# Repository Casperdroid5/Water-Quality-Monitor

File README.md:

# Water Quality Monitor

This document outlines my contribution to the Water Quality Monitor project during my internship at the Health Concept Lab.

## Overview

The Water Quality Monitor utilizes a Raspberry Pi running Raspbian as the main controller and computer, along with a custom-designed PCB for circuit layout. Hardware control, GUI, and data processing are implemented using Python.

## Design Process

The design process involved selecting suitable hardware components, designing the PCB layout, and programming the firmware in Python.

1. **Hardware Selection**: Chose appropriate sensors, actuators, and electronic components to suit the needs of the clients setup.
2. **PCB Design**: Created a custom PCB layout to ensure optimal circuit connections.
3. **Firmware Development**: Developed the firmware using Python to enable hardware communication.
## Testing

Comprehensive testing was conducted to ensure accuracy and reliability.

1. **Hardware Testing**: Verified proper functionality of each hardware component on the printed circuitboard.
2. **Software Testing**: Thoroughly tested firmware for peripherals.

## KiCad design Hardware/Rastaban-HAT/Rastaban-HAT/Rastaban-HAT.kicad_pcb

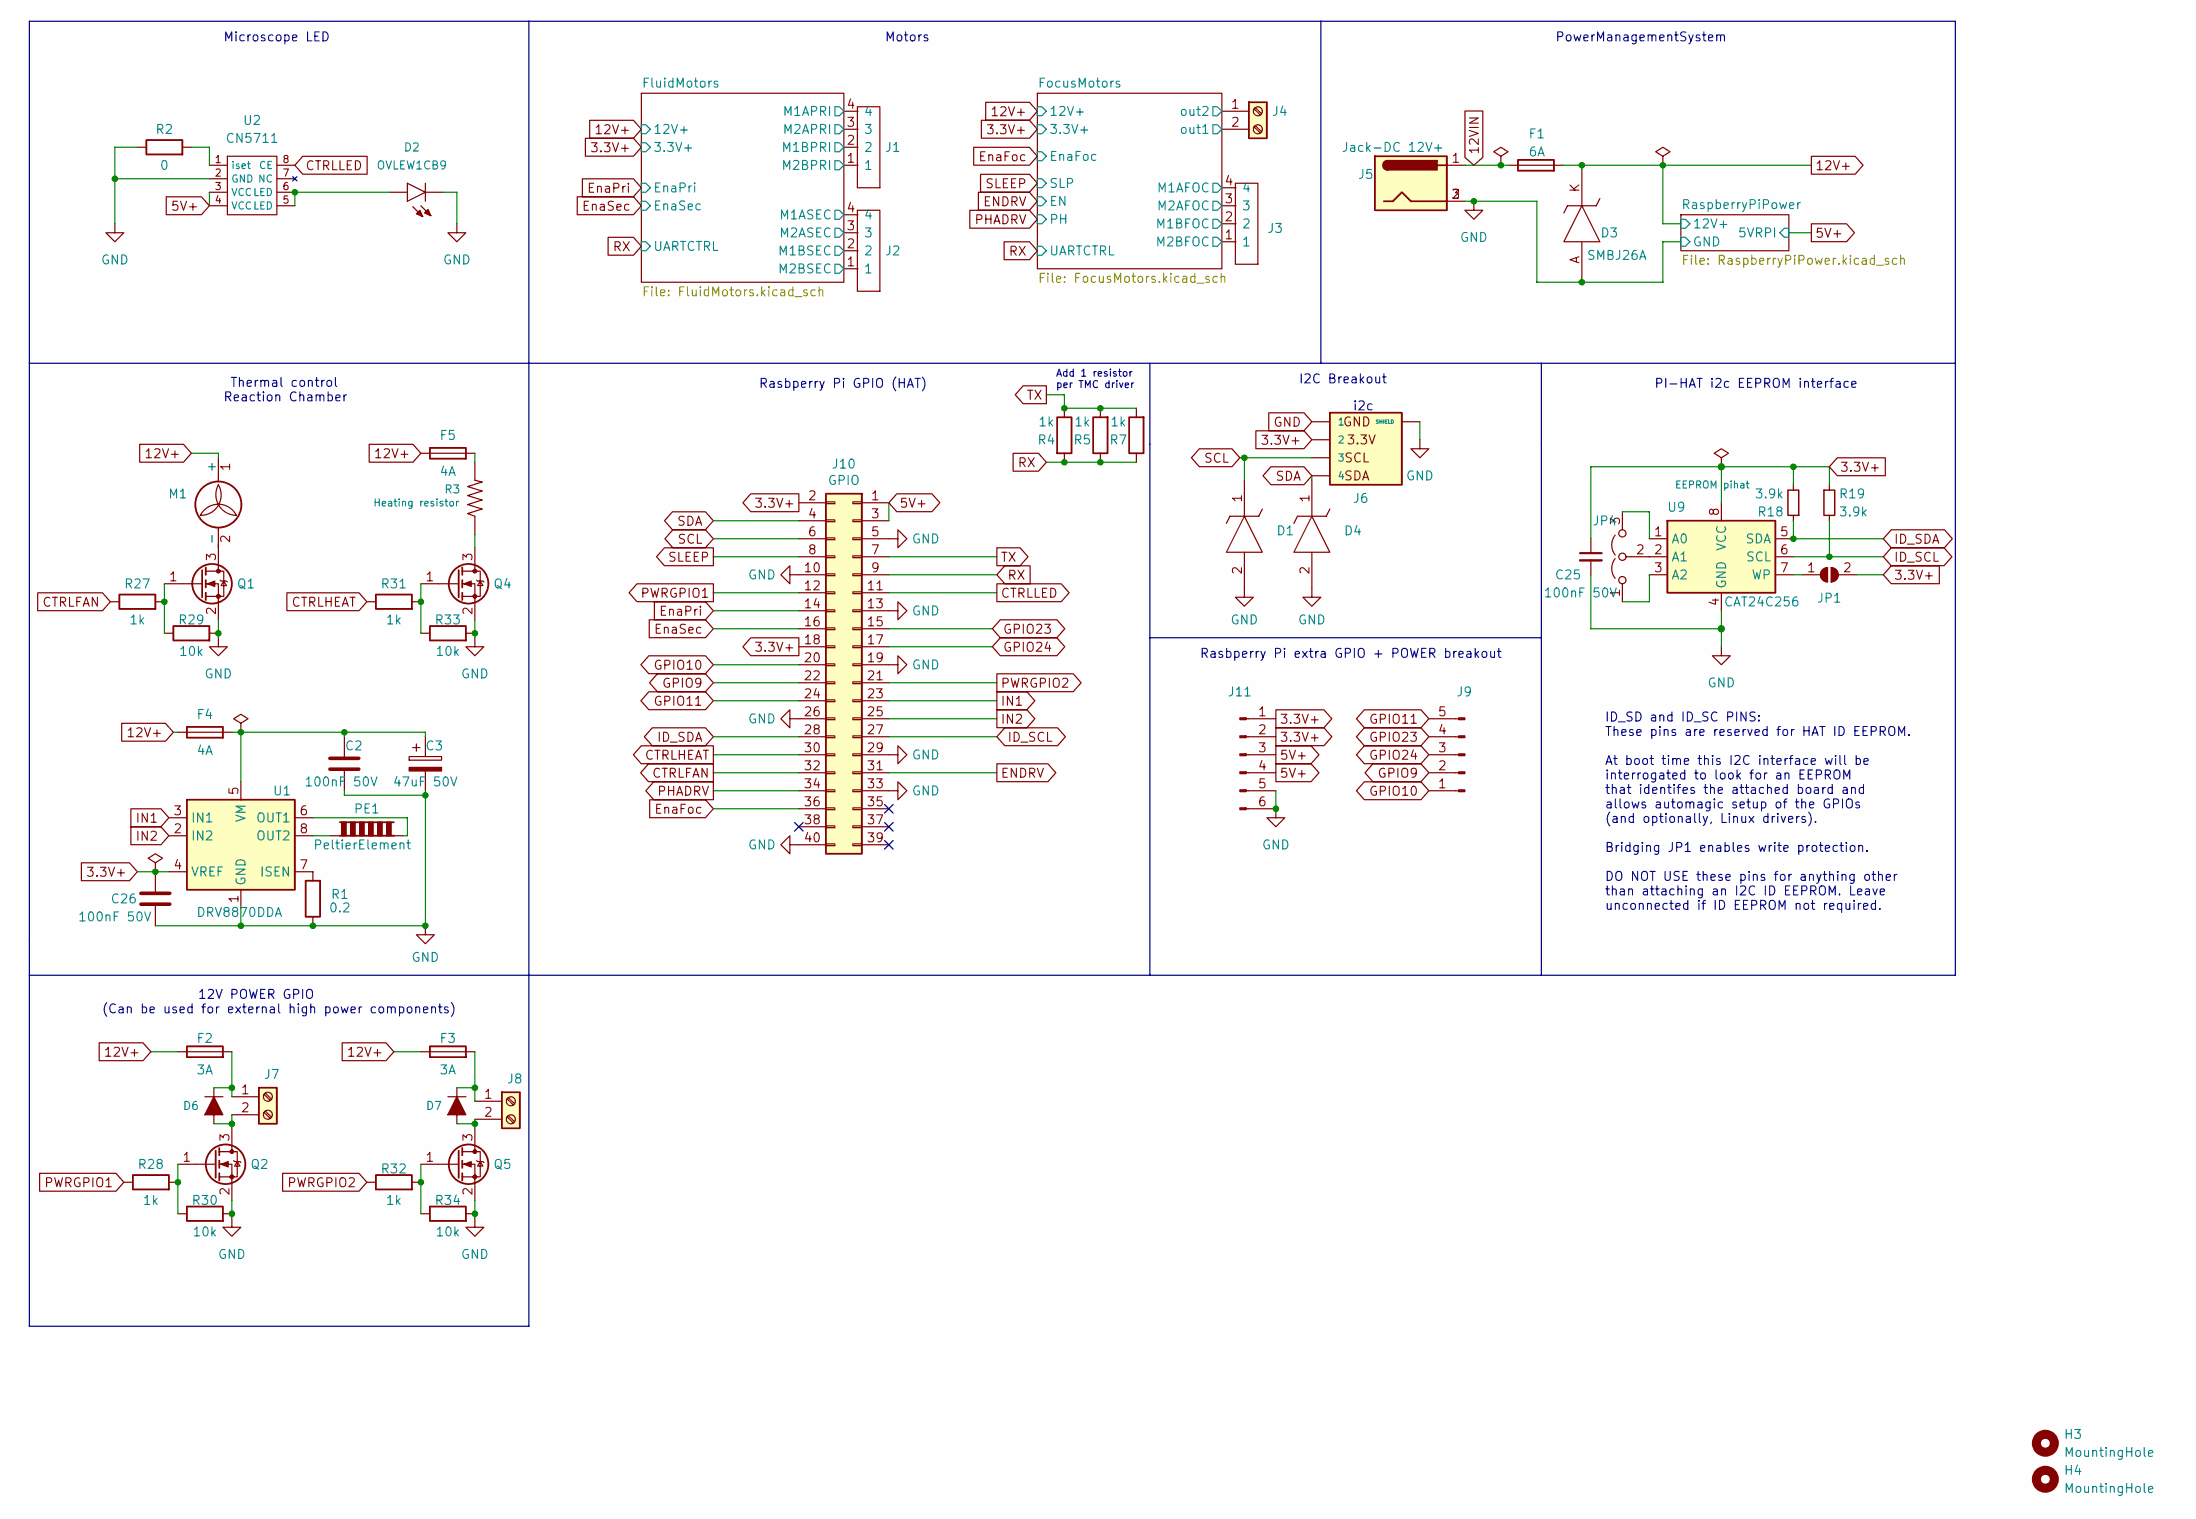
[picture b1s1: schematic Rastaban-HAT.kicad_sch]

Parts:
C2, C25, C26: 100nF 50V; C_0805_2012Metric_Pad1.18x1.45mm_HandSolder; LCSC C476766
C3: 47uF 50V; CP_Elec_6.3x5.4; Manufacturer_Part_Number C2918513; LCSC C72522
D1, D4: ESD7351HT1G; SOD2512X110N; Mouser Part Number 863-ESD7351HT1G
D2: OVLEW1CB9; 1808190; Mouser 828-OVLEW1CB9
D3: SMBJ26A; DIOM5436X261N; Mouser Part Number 652-SMBJ26A
D6, D7: DIODE-1N4148; D_1206_3216Metric_Pad1.42x1.75mm_HandSolder; LCSC C2128
F1: 6A; Fuse_2010_5025Metric_Pad1.52x2.65mm_HandSolder; LCSC C136353
F2, F3: 3A; Fuse_2010_5025Metric_Pad1.52x2.65mm_HandSolder; LCSC C355689
F4, F5: 4A; Fuse_2010_5025Metric_Pad1.52x2.65mm_HandSolder; LCSC C355687
H3, H4: MountingHole; MountingHole_2.7mm_M2.5
J1, J2, J3: 1778780; Mouser Part Number 651-1778780
J4, J7, J8: Screw_Terminal_01x02; 1808190; Mouser 651-1808190
J5: Jack-DC 12V+; BarrelJack_Wuerth_6941xx301002; Mouser 710-694106301002
J6: SM04B-SRSS-TB(LF)(SN); JST_SM04B-SRSS-TB(LF)(SN); LCSC C160404
J9: Conn_01x05_Male; PinHeader_1x05_P2.54mm_Vertical; LCSC x
J10: GPIO; PinHeader_2x20_P2.54mm_Vertical_SMD; Mouser 485-2187
J11: Conn_01x06_Male; PinSocket_1x06_P2.54mm_Vertical; LCSC x
JP1: ID_WP; SolderJumper-2_P1.3mm_Open_RoundedPad1.0x1.5mm; LCSC x
JP4: Jumper_3_Open; SolderJumper-3_P1.3mm_Open_Pad1.0x1.5mm_NumberLabels; LCSC x
M1: Fan; 1808190; Mouser 651-1808190
PE1: PeltierElement; 1808190; Mouser 651-1808190
Q1, Q2, Q4, Q5: PMV15ENE; SOT-23; Mouser 771-PMV15ENER
R1: 0.2; R_0805_2012Metric_Pad1.20x1.40mm_HandSolder; Mouser 771-PMV15ENER
R2: 0; R_0805_2012Metric_Pad1.20x1.40mm_HandSolder; LCSC C5140188
R3: 10W resistor; 1808190; LCSC x
R4, R5, R7, R27, R28, R31, R32: 1k; R_0805_2012Metric_Pad1.20x1.40mm_HandSolder; LCSC C17414
R18, R19: 3.9k; R_0805_2012Metric_Pad1.20x1.40mm_HandSolder; LCSC C2907252
R29, R30, R33, R34: 10k; R_0805_2012Metric_Pad1.20x1.40mm_HandSolder; LCSC C5140188
U1: DRV8870DDA; Texas_HTSOP-8-1EP_3.9x4.9mm_P1.27mm_EP2.95x4.9mm_Mask2.4x3.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; Mouser 595-DRV8870DDA
U2: CN5711; Texas_HTSOP-8-1EP_3.9x4.9mm_P1.27mm_EP2.95x4.9mm_Mask2.4x3.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; LCSC C35634
U9: CAT24C256; SOIC127P600X175-8N; Mouser 698-CAT24C256WI-GT3

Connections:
3.3V+: C25.1, C26.2, J6.2, J10.2, J10.18, J11.1, J11.2, JP1.2 (B), R18.2, R19.1, U1.4 (VREF), U9.8 (VCC); also elsewhere on the board
5V+: J10.1, J10.3, J11.3, J11.4, U2.3 (VCC), U2.4 (VCC); also elsewhere on the board
12V+: D3.K, F1.2, F2.1, F3.1, F4.1, F5.1, M1.1 (+); also elsewhere on the board
12VIN: F1.1, J5.1
/FluidMotors/M1APRI: J1.4; also elsewhere on the board
/FluidMotors/M1ASEC: J2.4; also elsewhere on the board
/FluidMotors/M1BPRI: J1.2; also elsewhere on the board
/FluidMotors/M1BSEC: J2.2; also elsewhere on the board
/FluidMotors/M2APRI: J1.3; also elsewhere on the board
/FluidMotors/M2ASEC: J2.3; also elsewhere on the board
/FluidMotors/M2BPRI: J1.1; also elsewhere on the board
/FluidMotors/M2BSEC: J2.1; also elsewhere on the board
/FocusMotors/M1AFOC: J3.4; also elsewhere on the board
/FocusMotors/M1BFOC: J3.2; also elsewhere on the board
/FocusMotors/M2AFOC: J3.3; also elsewhere on the board
/FocusMotors/M2BFOC: J3.1; also elsewhere on the board
/FocusMotors/out1: J4.2; also elsewhere on the board
/FocusMotors/out2: J4.1; also elsewhere on the board
CTRLFAN: J10.32, R27.1
CTRLHEAT: J10.30, R31.1
CTRLLED: J10.11, U2.8 (CE)
ENDRV: J10.31; also elsewhere on the board
EnaFoc: J10.36; also elsewhere on the board
EnaPri: J10.14; also elsewhere on the board
EnaSec: J10.16; also elsewhere on the board
GND: C2.1, C3.2, C25.2, C26.1, D1.2, D2.2 (C), D3.A, D4.2, J5.2, J5.3, J6.1, J6.S1 (SHIELD), J6.S2 (SHIELD), J10.5, J10.10, J10.13, J10.19, J10.26, J10.29, J10.33, J10.40, J11.5, J11.6, Q1.2 (S), Q2.2 (S), Q4.2 (S), Q5.2 (S), R1.1, R2.1, R29.2, R30.2, R33.2, R34.2, U1.1 (GND), U1.9 (GND), U2.2 (GND), U9.4 (GND); also elsewhere on the board
GPIO9: J9.2, J10.22
GPIO10: J9.1, J10.20
GPIO11: J9.5, J10.24
GPIO23: J9.4, J10.15
GPIO24: J9.3, J10.17
ID_SCL: J10.27, R19.2, U9.6 (SCL)
ID_SDA: J10.28, R18.1, U9.5 (SDA)
IN1: J10.23, U1.3 (IN1)
IN2: J10.25, U1.2 (IN2)
unnamed: C2.2, C3.1, F4.2, U1.5 (VM)
unnamed: D2.1 (A), U2.5 (LED), U2.6 (LED)
unnamed: D6.1 (C), F2.2, J7.1
unnamed: D6.2 (A), J7.2, Q2.3 (D)
unnamed: D7.1 (C), F3.2, J8.1
unnamed: D7.2 (A), J8.2, Q5.3 (D)
unnamed: F5.2, R3.2
unnamed: JP1.1 (A), U9.7 (WP)
unnamed: JP4.1 (A), U9.3 (A2)
unnamed: JP4.2 (C), U9.2 (A1)
unnamed: JP4.3 (B), U9.1 (A0)
unnamed: M1.2 (-), Q1.3 (D)
unnamed: PE1.1, U1.8 (OUT2)
unnamed: PE1.2, U1.6 (OUT1)
unnamed: Q1.1 (G), R27.2, R29.1
unnamed: Q2.1 (G), R28.2, R30.1
unnamed: Q4.1 (G), R31.2, R33.1
unnamed: Q4.3 (D), R3.1
unnamed: Q5.1 (G), R32.2, R34.1
unnamed: R1.2, U1.7 (ISEN)
unnamed: R2.2, U2.1 (iset)
PHADRV: J10.34; also elsewhere on the board
PWRGPIO1: J10.12, R28.1
PWRGPIO2: J10.21, R32.1
RX: J10.9, R4.2, R5.1, R7.1; also elsewhere on the board
SCL: D1.1, J6.3, J10.6
SDA: D4.1, J6.4, J10.4
SLEEP: J10.8; also elsewhere on the board
TX: J10.7, R4.1, R5.2, R7.2

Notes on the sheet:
ID_SD and ID_SC PINS: These pins are reserved for HAT ID EEPROM. At boot time this I2C interface will be interrogated to look for an EEPROM that identifes the attached board and allows automagic setup of the GPIOs (and optionally, Linux drivers). Bridging JP1 enables write protection. DO NOT USE th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
Add 1 resistor per TMC driver
I2C Breakout
Microscope LED
Rasbperry Pi extra GPIO + POWER breakout
Motors
Thermal control Reaction Chamber
12V POWER GPIO (Can be used for external high power components)
i2c
Rasbperry Pi GPIO (HAT)
PI-HAT i2c EEPROM interface
PowerManagementSystem

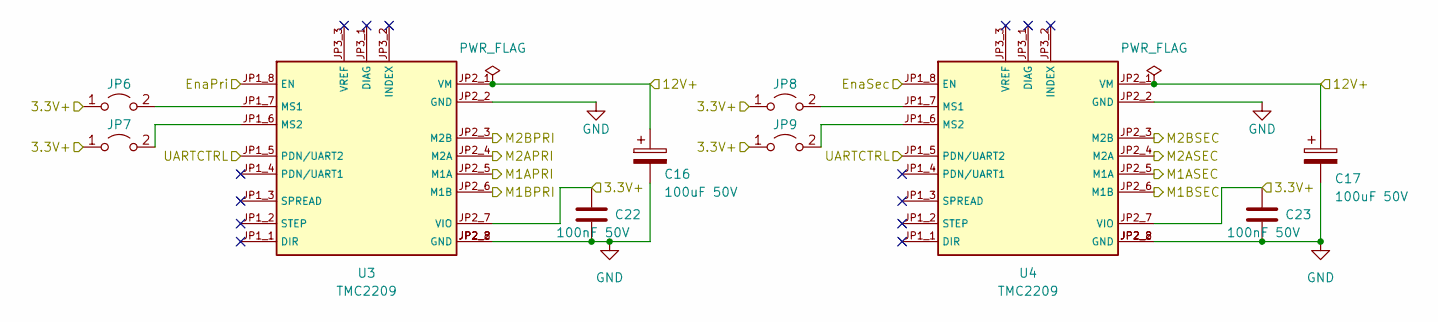
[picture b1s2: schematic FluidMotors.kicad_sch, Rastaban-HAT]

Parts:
C16, C17: 100uF 50V; CP_Elec_8x10; Manufacturer_Part_Number C3339; LCSC C445063
C22, C23: 100nF 50V; C_0805_2012Metric_Pad1.18x1.45mm_HandSolder; LCSC C476766
JP6, JP7, JP8, JP9: Jumper_2_Open; SolderJumper-2_P1.3mm_Open_RoundedPad1.0x1.5mm
U3, U4: TMC2209; MODULE_TMC2208_SILENTSTEPSTICK

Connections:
3.3V+: C22.1, C23.1, JP6.1 (A), JP7.1 (A), JP8.1 (A), JP9.1 (A), U3.JP2_7 (VIO), U4.JP2_7 (VIO); also elsewhere on the board
12V+: C16.1, C17.1, U3.JP2_1 (VM), U4.JP2_1 (VM); also elsewhere on the board
/FluidMotors/M1APRI: U3.JP2_5 (M1A); also elsewhere on the board
/FluidMotors/M1ASEC: U4.JP2_5 (M1A); also elsewhere on the board
/FluidMotors/M1BPRI: U3.JP2_6 (M1B); also elsewhere on the board
/FluidMotors/M1BSEC: U4.JP2_6 (M1B); also elsewhere on the board
/FluidMotors/M2APRI: U3.JP2_4 (M2A); also elsewhere on the board
/FluidMotors/M2ASEC: U4.JP2_4 (M2A); also elsewhere on the board
/FluidMotors/M2BPRI: U3.JP2_3 (M2B); also elsewhere on the board
/FluidMotors/M2BSEC: U4.JP2_3 (M2B); also elsewhere on the board
EnaPri: U3.JP1_8 (EN); also elsewhere on the board
EnaSec: U4.JP1_8 (EN); also elsewhere on the board
GND: C16.2, C17.2, C22.2, C23.2, U3.JP2_2 (GND), U3.JP2_8 (GND), U4.JP2_2 (GND), U4.JP2_8 (GND); also elsewhere on the board
unnamed: JP6.2 (B), U3.JP1_7 (MS1)
unnamed: JP7.2 (B), U3.JP1_6 (MS2)
unnamed: JP8.2 (B), U4.JP1_7 (MS1)
unnamed: JP9.2 (B), U4.JP1_6 (MS2)
RX: U3.JP1_5 (PDN/UART2), U4.JP1_5 (PDN/UART2); also elsewhere on the board

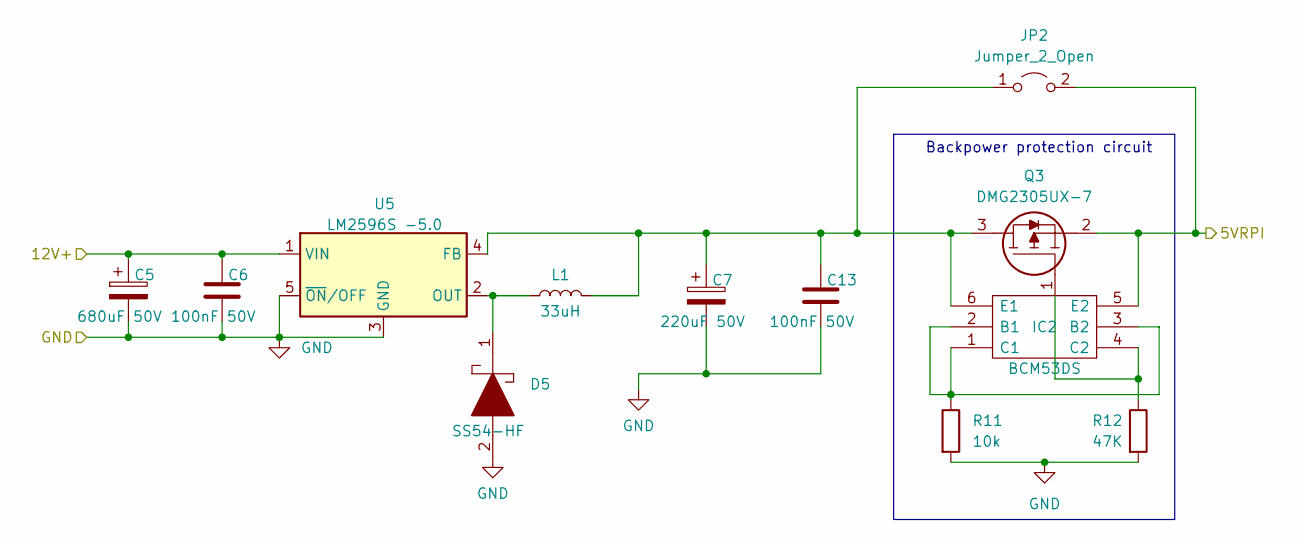
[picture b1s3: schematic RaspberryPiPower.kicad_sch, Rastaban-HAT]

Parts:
C5: 680uF 50V; CP_Elec_8x10; Manufacturer_Part_Number C3339; LCSC C445063
C6: 100nF 50V; C_0805_2012Metric_Pad1.18x1.45mm_HandSolder; LCSC C15850
C7: 220uF 50V; CP_Elec_8x10; Manufacturer_Part_Number C3339; LCSC C445063
C13: 100nF 50V; C_0805_2012Metric_Pad1.18x1.45mm_HandSolder; LCSC C476766
D5: SS54-HF; DIOM5025X220N; Mouser Part Number 750-SS54-HF
IC2: BCM53DS; SOT95P280X145-6N; Mouser Part Number 771-BCM53DSF
JP2: Jumper_2_Open; SolderJumper-2_P1.3mm_Open_RoundedPad1.0x1.5mm
L1: 33uH; L_Bourns_SRR1208_12.7x12.7mm; LCSC C82571
Q3: DMG2305UX-7; SOT-23; LCSC C2940629
R11: 10k; R_0805_2012Metric_Pad1.20x1.40mm_HandSolder; LCSC C5140188
R12: 47K; R_0805_2012Metric_Pad1.20x1.40mm_HandSolder; LCSC C102018
U5: LM2596S -5.0; TO-263-5_TabPin3

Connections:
5V+: IC2.5 (E2), JP2.2 (B), Q3.2; also elsewhere on the board
12V+: C5.1, C6.1, U5.1 (VIN); also elsewhere on the board
GND: C5.2, C6.2, C7.2, C13.1, D5.2, R11.2, R12.2, U5.3 (GND), U5.5 (~ON/OFF); also elsewhere on the board
unnamed: C7.1, C13.2, IC2.6 (E1), JP2.1 (A), L1.2, Q3.3, U5.4 (FB)
unnamed: D5.1, L1.1, U5.2 (OUT)
unnamed: IC2.1 (C1), IC2.2 (B1), IC2.3 (B2), R11.1
unnamed: IC2.4 (C2), Q3.1, R12.1

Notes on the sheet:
Backpower protection circuit

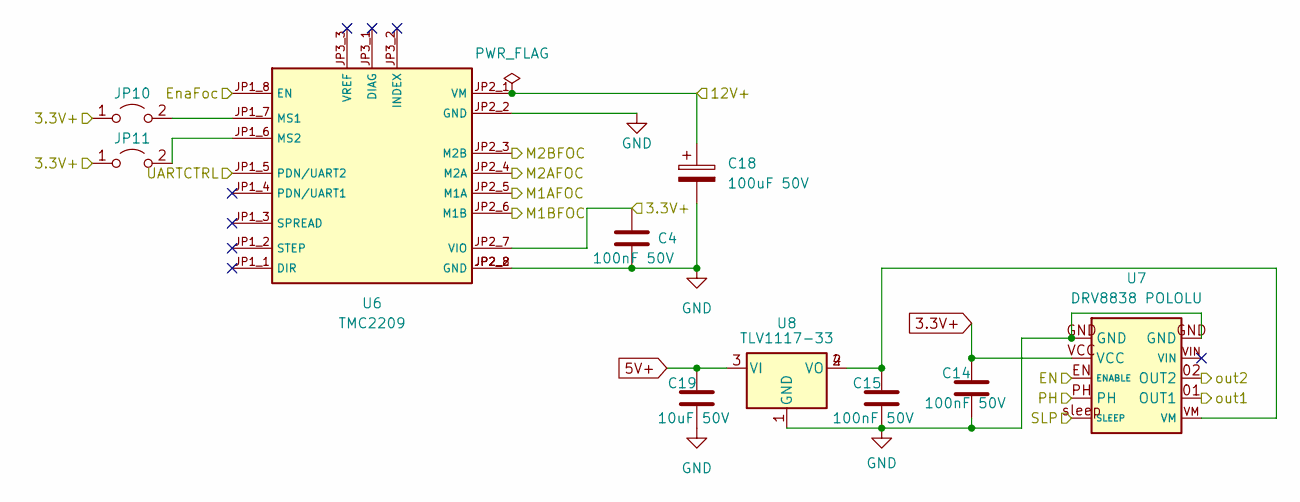
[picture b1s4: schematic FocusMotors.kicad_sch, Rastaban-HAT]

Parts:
C4, C14, C15: 100nF 50V; C_0805_2012Metric_Pad1.18x1.45mm_HandSolder; LCSC C476766
C18: 100uF 50V; CP_Elec_8x10; Manufacturer_Part_Number C3339; LCSC C445063
C19: 10uF 50V; C_0805_2012Metric_Pad1.18x1.45mm_HandSolder; Manufacturer_Part_Number C9807; LCSC C15850
JP10, JP11: Jumper_2_Open; SolderJumper-2_P1.3mm_Open_RoundedPad1.0x1.5mm
U6: TMC2209; MODULE_TMC2208_SILENTSTEPSTICK
U7: DRV8838 POLOLU
U8: TLV1117-33; SOT230P700X180-4N; LCSC C37359

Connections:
3.3V+: C4.1, C14.1, JP10.1 (A), JP11.1 (A), U6.JP2_7 (VIO), U7.VCC; also elsewhere on the board
5V+: C19.1, U8.3 (VI); also elsewhere on the board
12V+: C18.1, U6.JP2_1 (VM); also elsewhere on the board
/FocusMotors/M1AFOC: U6.JP2_5 (M1A); also elsewhere on the board
/FocusMotors/M1BFOC: U6.JP2_6 (M1B); also elsewhere on the board
/FocusMotors/M2AFOC: U6.JP2_4 (M2A); also elsewhere on the board
/FocusMotors/M2BFOC: U6.JP2_3 (M2B); also elsewhere on the board
/FocusMotors/out1: U7.01 (OUT1); also elsewhere on the board
/FocusMotors/out2: U7.02 (OUT2); also elsewhere on the board
ENDRV: U7.EN (ENABLE); also elsewhere on the board
EnaFoc: U6.JP1_8 (EN); also elsewhere on the board
GND: C4.2, C14.2, C15.1, C18.2, C19.2, U6.JP2_2 (GND), U6.JP2_8 (GND), U7.GND, U8.1 (GND); also elsewhere on the board
unnamed: C15.2, U7.VM, U8.2 (VO), U8.4 (VO)
unnamed: JP10.2 (B), U6.JP1_7 (MS1)
unnamed: JP11.2 (B), U6.JP1_6 (MS2)
PHADRV: U7.PH; also elsewhere on the board
RX: U6.JP1_5 (PDN/UART2); also elsewhere on the board
SLEEP: U7.~sleep (SLEEP); also elsewhere on the board

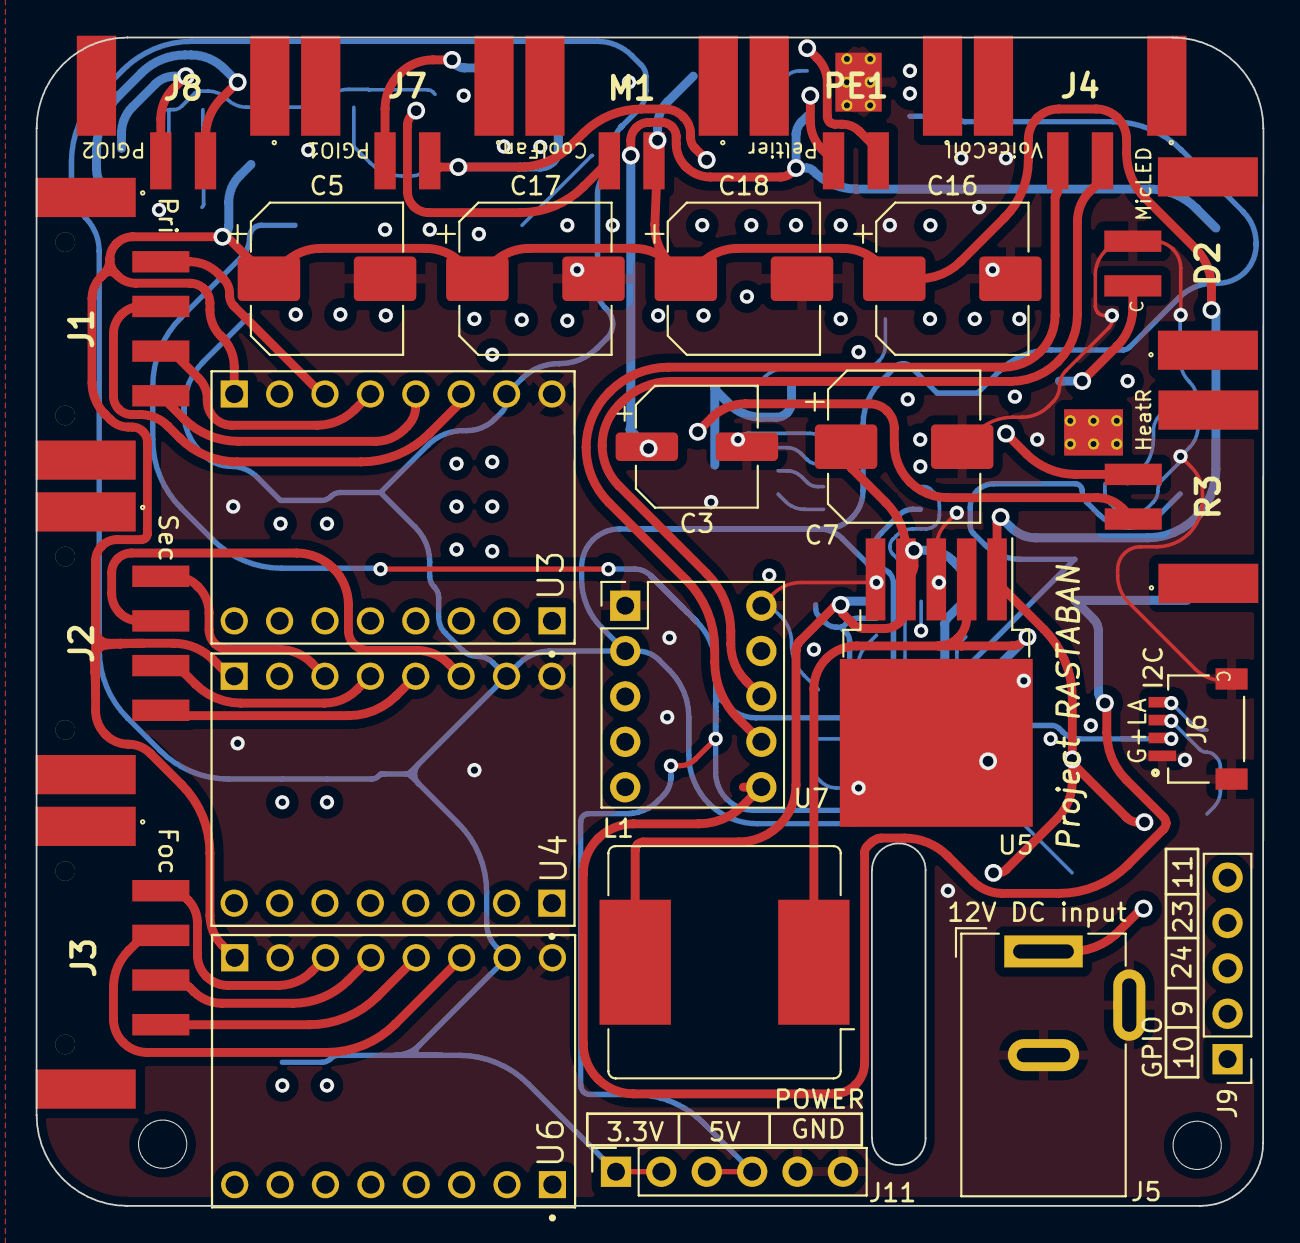
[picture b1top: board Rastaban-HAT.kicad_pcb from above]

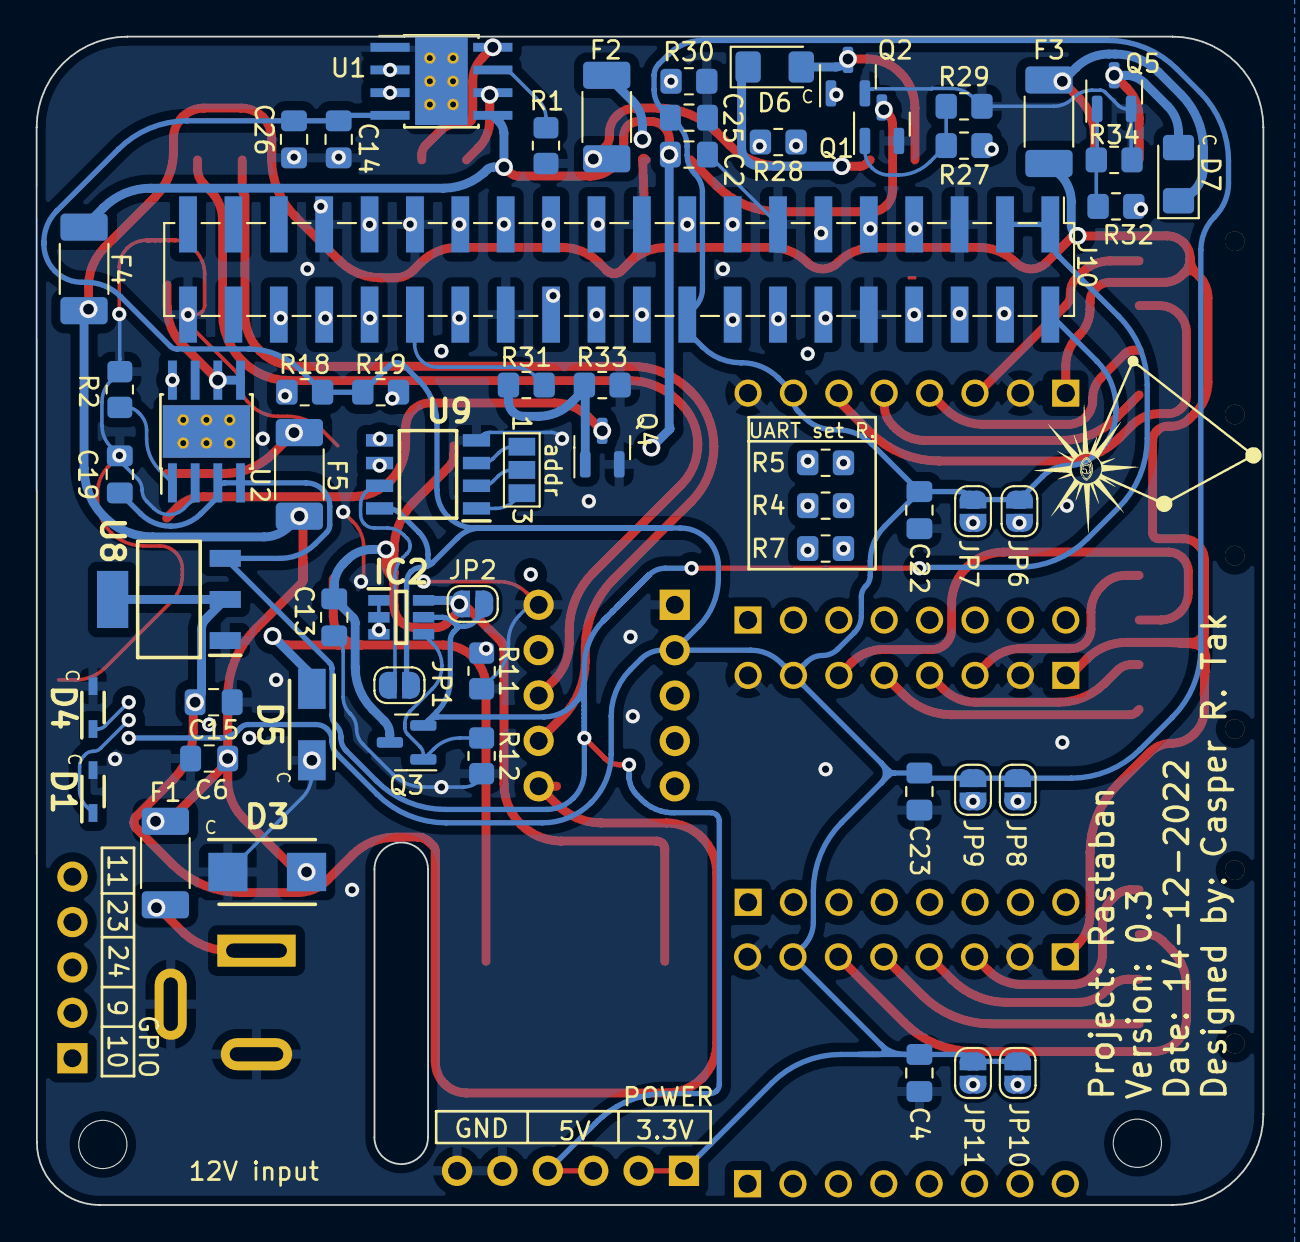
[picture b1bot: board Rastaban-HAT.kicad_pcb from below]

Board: 4 copper layers, 68.7 x 65.4 mm, 87 parts (59 on the bottom side), 75 nets.

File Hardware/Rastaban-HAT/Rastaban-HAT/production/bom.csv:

Designator,Footprint,Quantity,Value,LCSC Part #
"C13, C14, C15, C2, C22, C23, C25, C26, C4, C6",C_0805_2012Metric_Pad1.18x1.45mm_HandSolder,10,100nF 50V,C476766
"C16, C17, C18, C5",CP_Elec_8x10,4,100uF 50V,C445063
C19,C_0805_2012Metric_Pad1.18x1.45mm_HandSolder,1,10uF 50V,C15850
C3,CP_Elec_6.3x5.4,1,47uF 50V,C72522
C7,CP_Elec_8x10,1,220uF 50V,C445063
"D1, D4",SOD2512X110N,2,ESD7351HT1G,
D2,1808190,1,OVLEW1CB9,
D3,DIOM5436X261N,1,SMBJ26A,C10216
D5,DIOM5025X220N,1,SS54-HF ,
"D6, D7",D_1206_3216Metric_Pad1.42x1.75mm_HandSolder,2,DIODE-1N4148,C2128
F1,Fuse_2010_5025Metric_Pad1.52x2.65mm_HandSolder,1,6A,C136353
"F2, F3",Fuse_2010_5025Metric_Pad1.52x2.65mm_HandSolder,2,3A,C355689
"F4, F5",Fuse_2010_5025Metric_Pad1.52x2.65mm_HandSolder,2,4A,C355687
"H3, H4",MountingHole_2.7mm_M2.5,2,MountingHole,
IC2,SOT95P280X145-6N,1,BCM53DS,
"J1, J2, J3",1778780,3,1778780,C5173835
J10,PinHeader_2x20_P2.54mm_Vertical_SMD,1,GPIO,
J11,PinSocket_1x06_P2.54mm_Vertical,1,Conn_01x06_Male,x
"J4, J7, J8",1808190,3,Screw_Terminal_01x02,
J5,BarrelJack_Wuerth_6941xx301002,1,Jack-DC 12V+,
J6,JST_SM04B-SRSS-TB(LF)(SN),1,SM04B-SRSS-TB(LF)(SN),C160404
J9,PinHeader_1x05_P2.54mm_Vertical,1,Conn_01x05_Male,x
JP1,SolderJumper-2_P1.3mm_Open_RoundedPad1.0x1.5mm,1,ID_WP,x
"JP10, JP11, JP2, JP6, JP7, JP8, JP9",SolderJumper-2_P1.3mm_Open_RoundedPad1.0x1.5mm,7,Jumper_2_Open,
JP4,SolderJumper-3_P1.3mm_Open_Pad1.0x1.5mm_NumberLabels,1,Jumper_3_Open,x
L1,L_Bourns_SRR1208_12.7x12.7mm,1,33uH,C82571
M1,1808190,1,Fan,
PE1,1808190,1,PeltierElement,
"Q1, Q2, Q4, Q5",SOT-23,4,PMV15ENE,
Q3,SOT-23,1,DMG2305UX-7,C2940629
R1,R_0805_2012Metric_Pad1.20x1.40mm_HandSolder,1,0.2,
"R11, R29, R30, R33, R34",R_0805_2012Metric_Pad1.20x1.40mm_HandSolder,5,10k,C5140188
R12,R_0805_2012Metric_Pad1.20x1.40mm_HandSolder,1,47K,C102018
"R18, R19",R_0805_2012Metric_Pad1.20x1.40mm_HandSolder,2,3.9k,C2907252
R2,R_0805_2012Metric_Pad1.20x1.40mm_HandSolder,1,0,C5140188
"R27, R28, R31, R32, R4, R5, R7",R_0805_2012Metric_Pad1.20x1.40mm_HandSolder,7,1k,C17414
R3,1808190,1,10W resistor,x
U1,Texas_HTSOP-8-1EP_3.9x4.9mm_P1.27mm_EP2.95x4.9mm_Mask2.4x3.1mm_ThermalVias,1,DRV8870DDA,
U2,Texas_HTSOP-8-1EP_3.9x4.9mm_P1.27mm_EP2.95x4.9mm_Mask2.4x3.1mm_ThermalVias,1,CN5711,C35634
"U3, U4, U6",MODULE_TMC2208_SILENTSTEPSTICK,3,TMC2209,
U5,TO-263-5_TabPin3,1,LM2596S -5.0,
U7,DRV8838 POLOLU,1,DRV8838 POLOLU,
U8,SOT230P700X180-4N,1,TLV1117-33,C37359
U9,SOIC127P600X175-8N,1,CAT24C256,

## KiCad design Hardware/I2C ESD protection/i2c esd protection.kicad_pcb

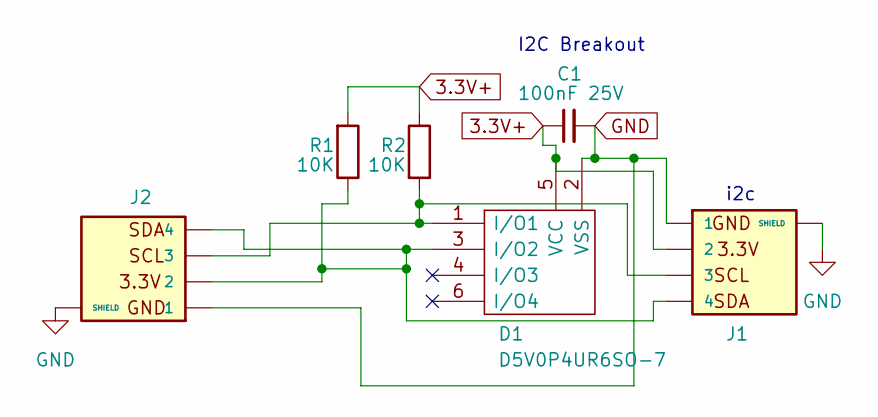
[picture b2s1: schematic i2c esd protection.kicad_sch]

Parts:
C1: 100nF 25V; C_0805_2012Metric_Pad1.18x1.45mm_HandSolder; LCSC C531179
D1: D5V0P4UR6SO-7; SOT95P285X140-6N; Mouser 621-D5V0P4UR6SO-7
J1, J2: SM04B-SRSS-TB(LF)(SN); JST_SM04B-SRSS-TB(LF)(SN); LCSC C160404
R1, R2: 10K; R_0805_2012Metric_Pad1.20x1.40mm_HandSolder; LCSC C5140188

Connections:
3.3V+: C1.1, D1.5 (VCC), J1.2, R1.2, R2.1
GND: C1.2, D1.2 (VSS), J1.1, J1.S1 (SHIELD), J1.S2 (SHIELD), J2.1, J2.S1 (SHIELD), J2.S2 (SHIELD)
unnamed: D1.1 (I/O1), J1.3, J2.3, R2.2
unnamed: D1.3 (I/O2), J1.4, J2.2, J2.4, R1.1

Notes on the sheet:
I2C Breakout
i2c

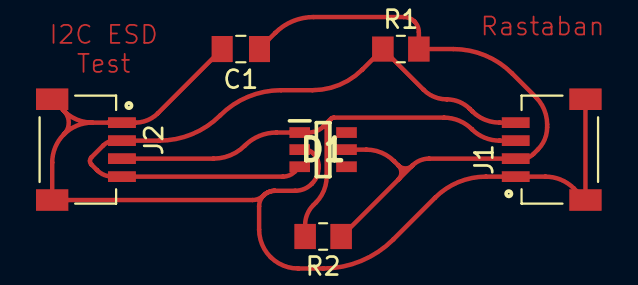
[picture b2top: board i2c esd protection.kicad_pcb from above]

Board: 2 copper layers, 6 parts (0 on the bottom side), 4 nets.

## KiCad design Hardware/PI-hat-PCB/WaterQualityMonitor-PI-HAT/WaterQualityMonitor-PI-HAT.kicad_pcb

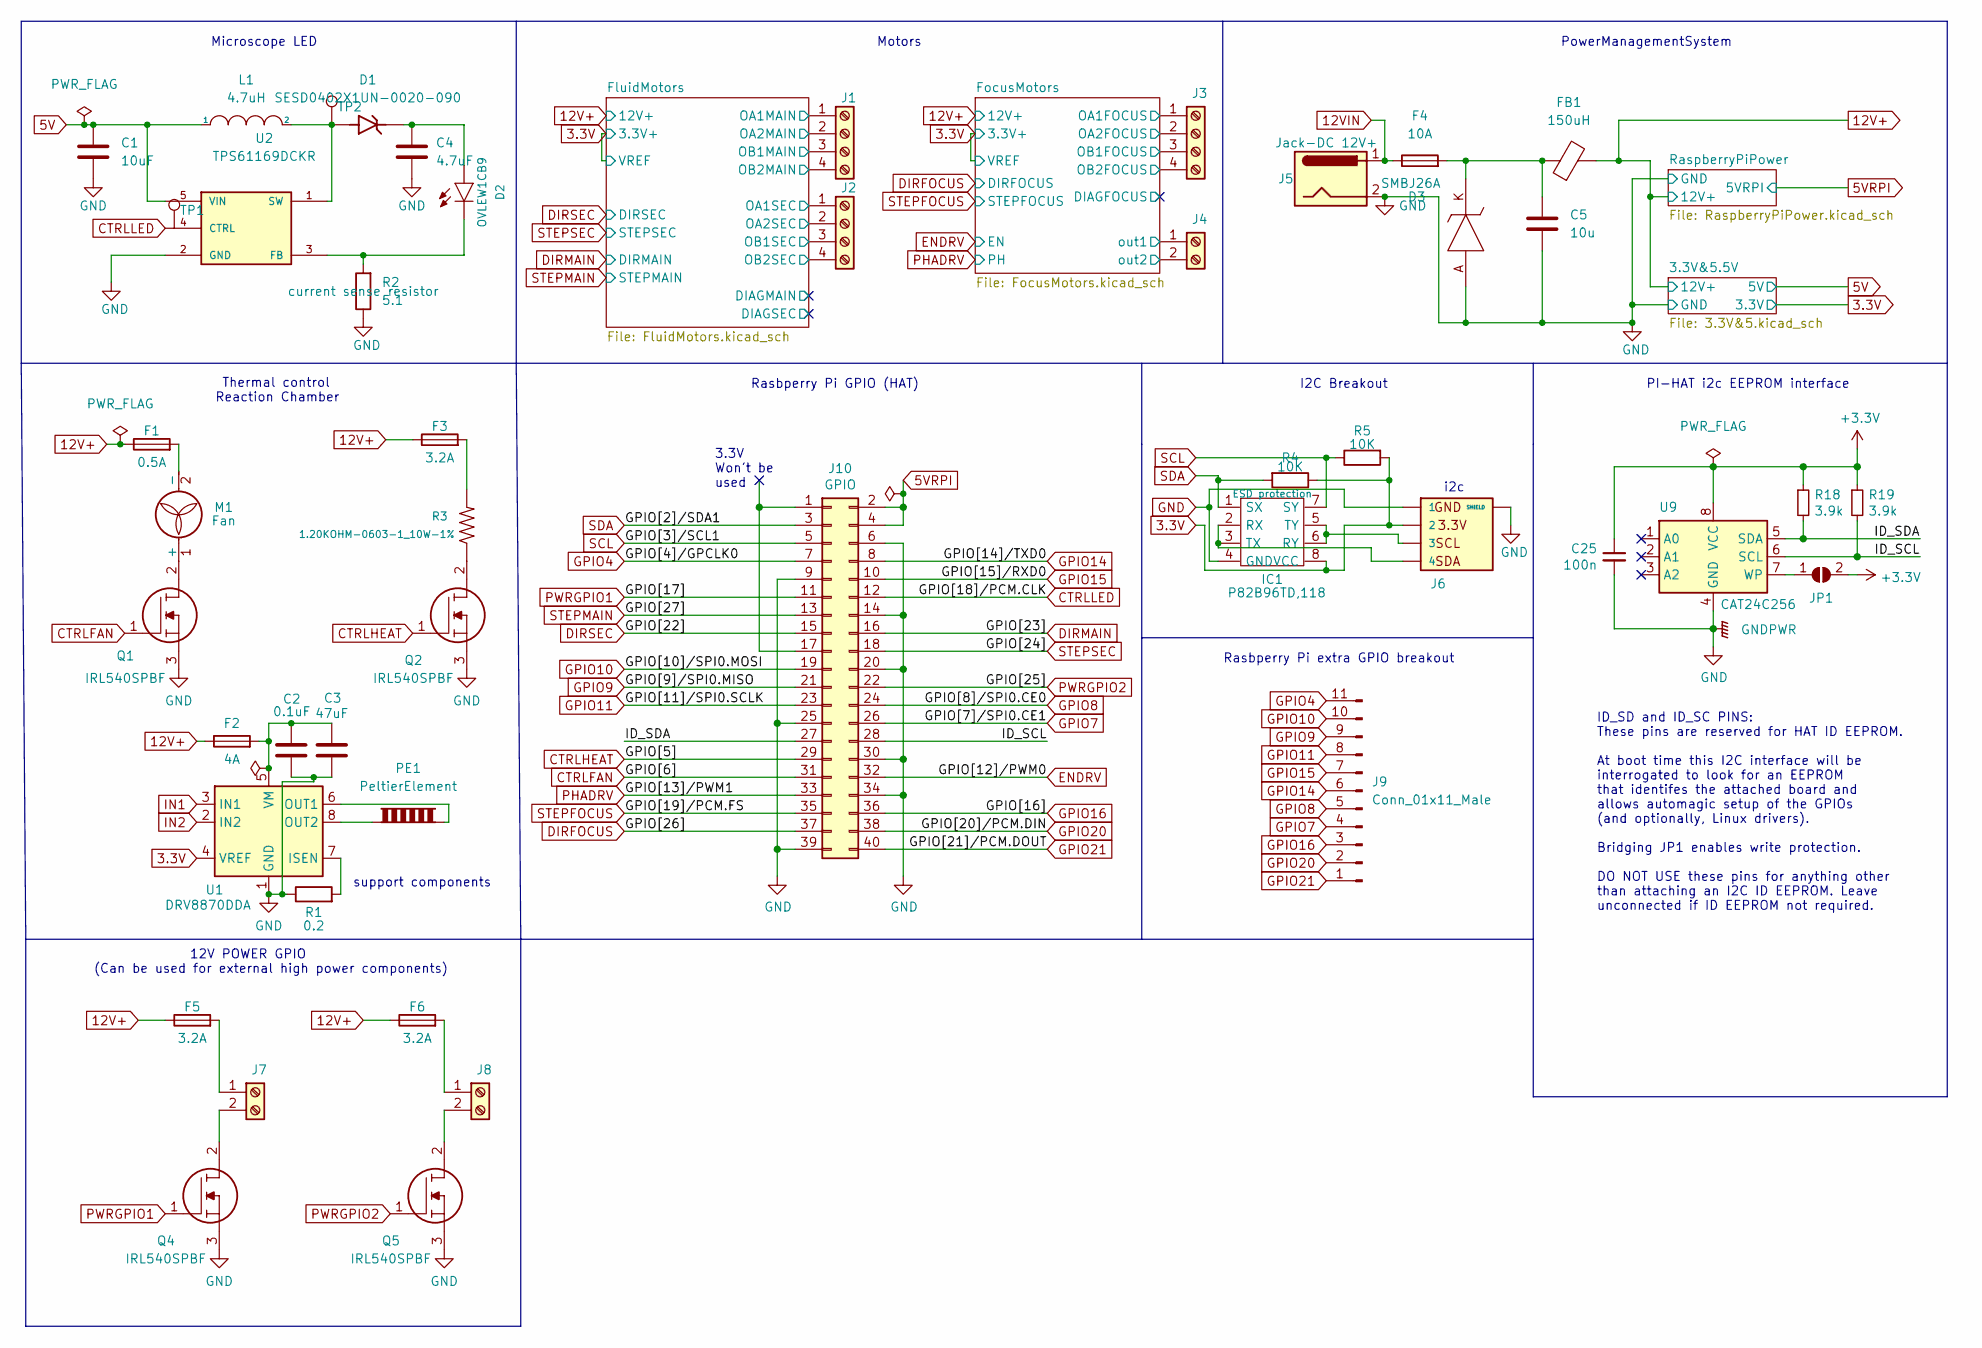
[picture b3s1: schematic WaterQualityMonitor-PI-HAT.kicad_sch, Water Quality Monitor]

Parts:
C1: 10uF; SOIC127P600X175-8N
C2: 0.1uF; C_1206_3216Metric_Pad1.33x1.80mm_HandSolder
C3: 47uF; C_1206_3216Metric_Pad1.33x1.80mm_HandSolder
C4: 4.7uF; C_1206_3216Metric_Pad1.33x1.80mm_HandSolder
C5: 10u; C_1206_3216Metric_Pad1.33x1.80mm_HandSolder
C25: 100n; C_1206_3216Metric_Pad1.33x1.80mm_HandSolder
D1: SESD0402X1UN-0020-090; SESD0402X1UN0020090; PARTREV 08/22/19
D2: OVLEW1CB9
D3: SMBJ26A; DIOM4336X265N; Mouser Part Number 652-SMBJ26A
F1: 0.5A; Fuse_1206_3216Metric_Pad1.42x1.75mm_HandSolder
F2: 4A; Fuse_1206_3216Metric_Pad1.42x1.75mm_HandSolder
F3, F5, F6: 3.2A; Fuse_1206_3216Metric_Pad1.42x1.75mm_HandSolder
F4: 10A; Fuse_1206_3216Metric_Pad1.42x1.75mm_HandSolder
FB1: 150uH; L_1206_3216Metric_Pad1.22x1.90mm_HandSolder
IC1: P82B96TD,118; SOIC127P600X175-8N; Mouser Part Number 771-P82B96TD-T
J1, J2, J3: Screw_Terminal_01x04; TerminalBlock_Altech_AK300-4_P5.00mm
J4, J7, J8: Screw_Terminal_01x02; TerminalBlock_Altech_AK300-2_P5.00mm
J5: Jack-DC 12V+; BarrelJack_Wuerth_6941xx301002
J6: SM04B-SRSS-TB(LF)(SN); JST_SM04B-SRSS-TB(LF)(SN)
J9: Conn_01x11_Male; PinHeader_1x11_P2.54mm_Vertical
J10: GPIO; PinSocket_2x20_P2.54mm_Vertical
JP1: ID_WP; SolderJumper-2_P1.3mm_Open_RoundedPad1.0x1.5mm
L1: 4.7uH; L_1206_3216Metric_Pad1.22x1.90mm_HandSolder
M1: Fan; PinHeader_1x02_P2.54mm_Vertical
PE1: PeltierElement; TerminalBlock_Altech_AK300-2_P5.00mm
Q1, Q2, Q4, Q5: IRL540SPBF; Mouser Part Number 844-IRL540SPBF
R1: 0.2; R_1206_3216Metric_Pad1.30x1.75mm_HandSolder
R2: 5.1; R_1206_3216Metric_Pad1.30x1.75mm_HandSolder
R3: 1.20KOHM-0603-1_10W-1%; R_1206_3216Metric_Pad1.30x1.75mm_HandSolder
R4, R5: 10K; R_1206_3216Metric_Pad1.30x1.75mm_HandSolder
R18, R19: 3.9k; R_1206_3216Metric_Pad1.30x1.75mm_HandSolder
TP1, TP2: TestPoint; TestPoint_Keystone_5019_Minature
U1: DRV8870DDA; Texas_HTSOP-8-1EP_3.9x4.9mm_P1.27mm_EP2.95x4.9mm_Mask2.4x3.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
U2: TPS61169DCKR; SOT65P210X110-5N; PARTREV A
U9: CAT24C256; SOIC127P600X175-8N

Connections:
3.3V: IC1.8 (VCC), J6.2, R4.1, R5.2, U1.4 (VREF); also elsewhere on the board
5V: C1.1, L1.1, U2.5 (VIN); also elsewhere on the board
5VRPI: J10.2, J10.4; also elsewhere on the board
12V+: F1.1, F2.1, F3.1, F5.1, F6.1, FB1.2; also elsewhere on the board
12VIN: F4.1, J5.1
+3V3: C25.1, JP1.2 (B), R18.1, R19.1, U9.8 (VCC)
/FluidMotors/OA1MAIN: J1.1; also elsewhere on the board
/FluidMotors/OA1SEC: J2.1; also elsewhere on the board
/FluidMotors/OA2MAIN: J1.2; also elsewhere on the board
/FluidMotors/OA2SEC: J2.2; also elsewhere on the board
/FluidMotors/OB1MAIN: J1.3; also elsewhere on the board
/FluidMotors/OB1SEC: J2.3; also elsewhere on the board
/FluidMotors/OB2MAIN: J1.4; also elsewhere on the board
/FluidMotors/OB2SEC: J2.4; also elsewhere on the board
/FocusMotors/OA1FOCUS: J3.1; also elsewhere on the board
/FocusMotors/OA2FOCUS: J3.2; also elsewhere on the board
/FocusMotors/OB1FOCUS: J3.3; also elsewhere on the board
/FocusMotors/OB2FOCUS: J3.4; also elsewhere on the board
/FocusMotors/out1: J4.1; also elsewhere on the board
/FocusMotors/out2: J4.2; also elsewhere on the board
/ID_SCL: J10.28, R19.2, U9.6 (SCL)
/ID_SDA: J10.27, R18.2, U9.5 (SDA)
CTRLFAN: J10.31, Q1.1
CTRLHEAT: J10.29, Q2.1
CTRLLED: J10.12, U2.4 (CTRL)
DIRFOCUS: J10.37; also elsewhere on the board
DIRMAIN: J10.16; also elsewhere on the board
DIRSEC: J10.15; also elsewhere on the board
ENDRV: J10.32; also elsewhere on the board
GND: C1.2, C2.1, C3.1, C4.2, C5.2, C25.2, D3.A, IC1.4 (GND), J5.2, J6.1, J6.S1 (SHIELD), J6.S2 (SHIELD), J10.6, J10.9, J10.14, J10.20, J10.25, J10.30, J10.34, J10.39, Q1.3, Q2.3, Q4.3, Q5.3, R1.1, R2.1, U1.1 (GND), U1.9 (GND), U2.2 (GND), U9.4 (GND); also elsewhere on the board
GPIO4: J9.11, J10.7
GPIO7: J9.4, J10.26
GPIO8: J9.5, J10.24
GPIO9: J9.9, J10.21
GPIO10: J9.10, J10.19
GPIO11: J9.8, J10.23
GPIO14: J9.6, J10.8
GPIO15: J9.7, J10.10
GPIO16: J9.3, J10.36
GPIO20: J9.2, J10.38
GPIO21: J9.1, J10.40
IN1: U1.3 (IN1)
IN2: U1.2 (IN2)
unnamed: C2.2, C3.2, F2.2, U1.5 (VM)
unnamed: C4.1, D1.C (2), D2.A
unnamed: C5.1, D3.K, F4.2, FB1.1
unnamed: D1.A (1), L1.2, TP2.1, U2.1 (SW)
unnamed: D2.K (C), R2.2, U2.3 (FB)
unnamed: F1.2, M1.2 (-)
unnamed: F3.2, R3.2
unnamed: F5.2, J7.1
unnamed: F6.2, J8.1
unnamed: IC1.2 (RX), IC1.3 (TX), J6.4
unnamed: IC1.5 (TY), IC1.6 (RY), J6.3
unnamed: J7.2, Q4.2
unnamed: J8.2, Q5.2
unnamed: JP1.1 (A), U9.7 (WP)
unnamed: M1.1 (+), Q1.2
unnamed: PE1.1, U1.8 (OUT2)
unnamed: PE1.2, U1.6 (OUT1)
unnamed: Q2.2, R3.1
unnamed: R1.2, U1.7 (ISEN)
PHADRV: J10.33; also elsewhere on the board
PWRGPIO1: J10.11, Q4.1
PWRGPIO2: J10.22, Q5.1
SCL: IC1.7 (SY), J10.5, R5.1
SDA: IC1.1 (SX), J10.3, R4.2
STEPFOCUS: J10.35; also elsewhere on the board
STEPMAIN: J10.13; also elsewhere on the board
STEPSEC: J10.18; also elsewhere on the board

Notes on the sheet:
ID_SD and ID_SC PINS: These pins are reserved for HAT ID EEPROM. At boot time this I2C interface will be interrogated to look for an EEPROM that identifes the attached board and allows automagic setup of the GPIOs (and optionally, Linux drivers). Bridging JP1 enables write protection. DO NOT USE th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
I2C Breakout
Microscope LED
Rasbperry Pi extra GPIO breakout
Motors
support components
Thermal control Reaction Chamber
12V POWER GPIO (Can be used for external high power components)
i2c
3.3V Won't be used
Rasbperry Pi GPIO (HAT)
PI-HAT i2c EEPROM interface
PowerManagementSystem
